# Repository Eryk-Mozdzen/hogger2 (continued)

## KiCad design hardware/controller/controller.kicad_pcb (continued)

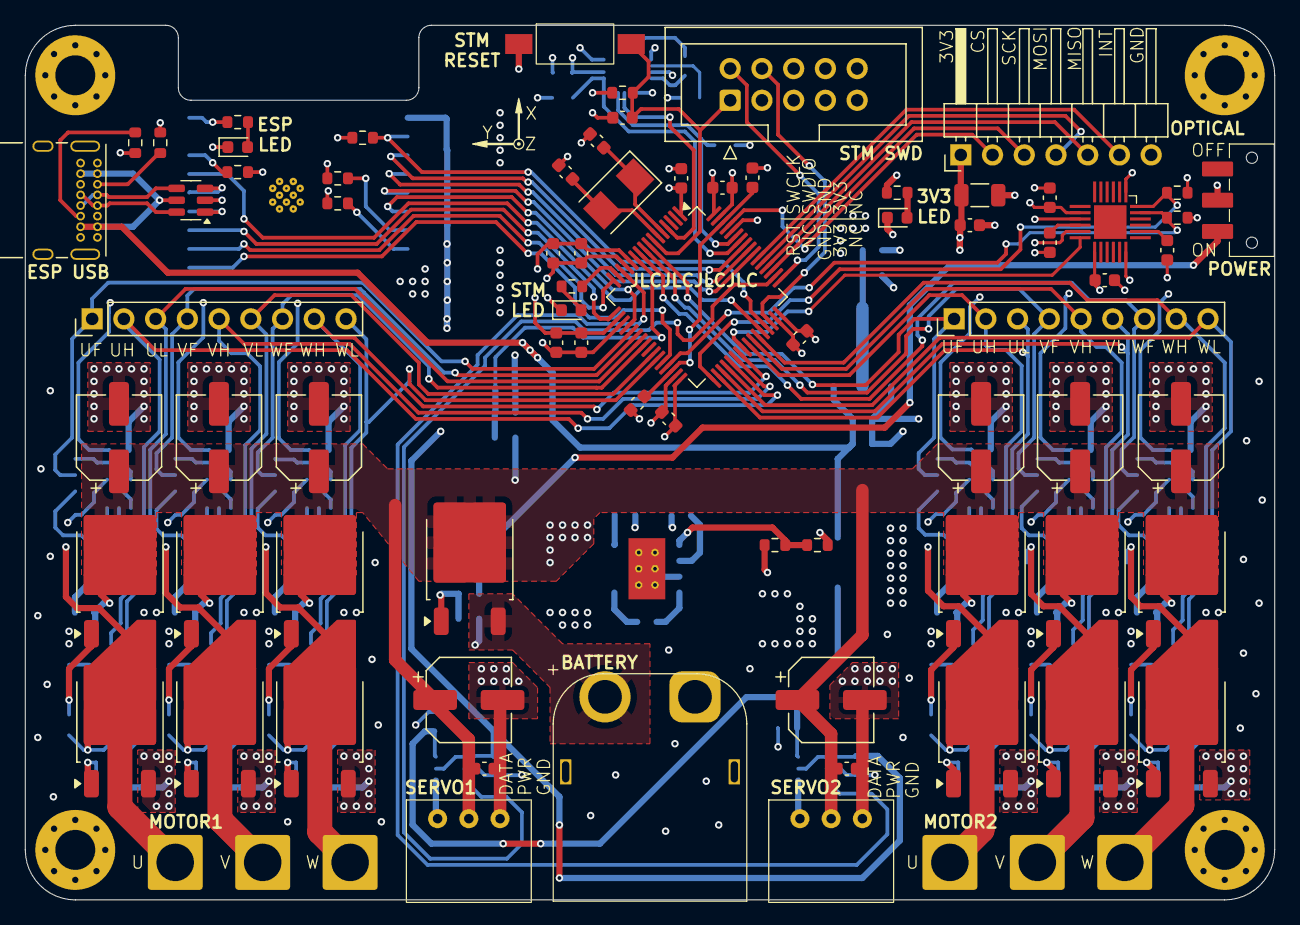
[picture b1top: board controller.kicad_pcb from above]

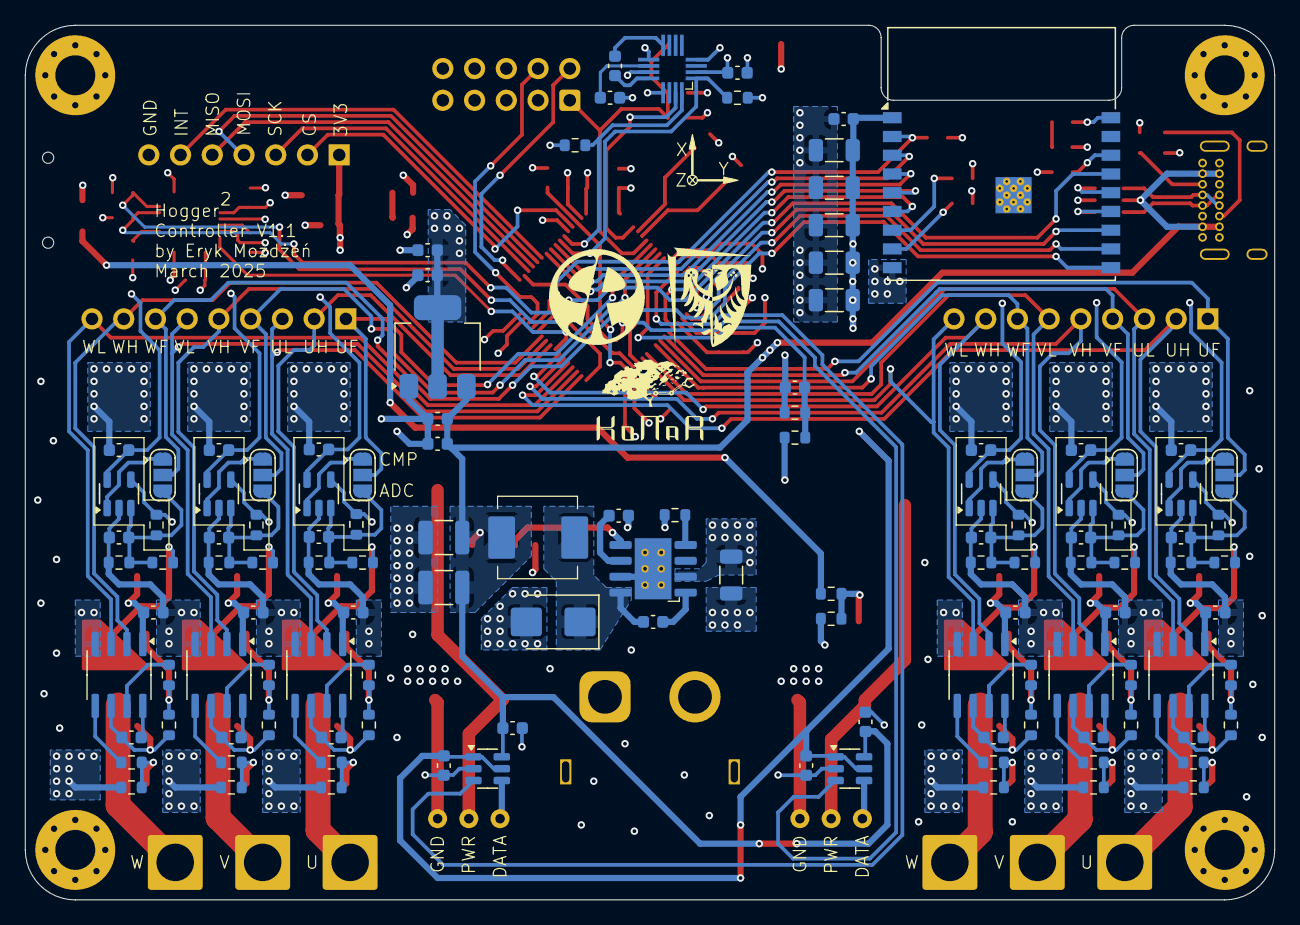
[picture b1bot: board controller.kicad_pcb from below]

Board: 4 copper layers, 100.0 x 70.0 mm, 205 parts (122 on the bottom side), 130 nets.

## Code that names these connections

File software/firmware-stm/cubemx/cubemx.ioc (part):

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Mcu.Name=STM32H523RETx
Mcu.Package=LQFP64
Mcu.UserName=STM32H523RETx
PA0.GPIOParameters=GPIO_Label
PA0.GPIO_Label=SERVO2_DATA
PA0.Mode=Half_duplex(single_wire_mode)
PA0.Signal=UART4_TX
PA1.GPIOParameters=GPIO_Label
PA1.GPIO_Label=LED
PA1.Signal=GPIO_Output
PA10.GPIOParameters=GPIO_Speed,GPIO_Label
PA10.GPIO_Label=MOTOR2_PWM_WH
PA10.GPIO_Speed=GPIO_SPEED_FREQ_LOW
PA10.Signal=S_TIM1_CH3
PA12.GPIOParameters=GPIO_PuPd,GPIO_Label,GPIO_ModeDefaultOutputPP
PA12.GPIO_Label=ESP_EN
PA12.GPIO_ModeDefaultOutputPP=GPIO_MODE_OUTPUT_OD
PA12.GPIO_PuPd=GPIO_NOPULL
PA12.Signal=GPIO_Output
PA15(JTDI).GPIOParameters=GPIO_Label
PA15(JTDI).GPIO_Label=SERVO1_DATA
PA15(JTDI).Mode=Half_duplex(single_wire_mode)
PA15(JTDI).Signal=USART1_TX
PA4.GPIOParameters=GPIO_Label
PA4.GPIO_Label=ESP_CS
PA4.Signal=GPIO_Output
PA5.GPIOParameters=GPIO_Label
PA5.GPIO_Label=MOTOR1_BEMF_U
PA5.Signal=ADCx_INP19
PA6.GPIOParameters=GPIO_Label
PA6.GPIO_Label=MOTOR1_BEMF_V
PA6.Signal=ADCx_INP3
PA7.GPIOParameters=GPIO_Speed,GPIO_Label
PA7.GPIO_Label=MOTOR1_PWM_UL
PA7.GPIO_Speed=GPIO_SPEED_FREQ_LOW
PA7.Mode=PWM Generation1 CH1 CH1N
PA7.Signal=TIM8_CH1N
PA8.GPIOParameters=GPIO_Speed,GPIO_Label
PA8.GPIO_Label=MOTOR2_PWM_UH
PA8.GPIO_Speed=GPIO_SPEED_FREQ_LOW
PA8.Signal=S_TIM1_CH1
PA9.GPIOParameters=GPIO_Speed,GPIO_Label
PA9.GPIO_Label=MOTOR2_PWM_VH
PA9.GPIO_Speed=GPIO_SPEED_FREQ_LOW
PA9.Signal=S_TIM1_CH2
PB0.GPIOParameters=GPIO_Speed,GPIO_Label
PB0.GPIO_Label=MOTOR1_PWM_VL
PB0.GPIO_Speed=GPIO_SPEED_FREQ_LOW
PB0.Mode=PWM Generation2 CH2 CH2N
PB0.Signal=TIM8_CH2N
PB1.GPIOParameters=GPIO_Speed,GPIO_Label
PB1.GPIO_Label=MOTOR1_PWM_WL
PB1.GPIO_Speed=GPIO_SPEED_FREQ_LOW
PB1.Mode=PWM Generation3 CH3 CH3N
PB1.Signal=TIM8_CH3N
PB10.GPIOParameters=GPIO_Label
PB10.GPIO_Label=IMU_SCL
PB10.Mode=I2C
PB10.Signal=I2C2_SCL
PB12.GPIOParameters=GPIO_Label
PB12.GPIO_Label=IMU_SDA
PB12.Mode=I2C
PB12.Signal=I2C2_SDA
PB13.GPIOParameters=GPIO_Speed,GPIO_Label
PB13.GPIO_Label=MOTOR2_PWM_UL
PB13.GPIO_Speed=GPIO_SPEED_FREQ_LOW
PB13.Mode=PWM Generation1 CH1 CH1N
PB13.Signal=TIM1_CH1N
PB14.GPIOParameters=GPIO_Speed,GPIO_Label
PB14.GPIO_Label=MOTOR2_PWM_VL
PB14.GPIO_Speed=GPIO_SPEED_FREQ_LOW
PB14.Mode=PWM Generation2 CH2 CH2N
PB14.Signal=TIM1_CH2N
PB15.GPIOParameters=GPIO_Speed,GPIO_Label
PB15.GPIO_Label=MOTOR2_PWM_WL
PB15.GPIO_Speed=GPIO_SPEED_FREQ_LOW
PB15.Mode=PWM Generation3 CH3 CH3N
PB15.Signal=TIM1_CH3N
PB2.GPIOParameters=GPIO_Label
PB2.GPIO_Label=ESP_HANDSHAKE
PB2.Signal=GPXTI2
PB3(JTDO/TRACESWO).GPIOParameters=GPIO_Label
PB3(JTDO/TRACESWO).GPIO_Label=ESP_SCK
PB3(JTDO/TRACESWO).Mode=Full_Duplex_Master
PB3(JTDO/TRACESWO).Signal=SPI1_SCK
PB4(NJTRST).GPIOParameters=GPIO_Label
PB4(NJTRST).GPIO_Label=ESP_MISO
PB4(NJTRST).Mode=Full_Duplex_Master
PB4(NJTRST).Signal=SPI1_MISO
PB5.GPIOParameters=GPIO_Label
PB5.GPIO_Label=ESP_MOSI
PB5.Mode=Full_Duplex_Master
PB5.Signal=SPI1_MOSI
PB6.GPIOParameters=GPIO_Label
PB6.GPIO_Label=MAG_SCL
PB6.Mode=I2C
PB6.Signal=I2C1_SCL
PB7.GPIOParameters=GPIO_Label
PB7.GPIO_Label=MAG_SDA
PB7.Mode=I2C
PB7.Signal=I2C1_SDA
PB8.GPIOParameters=GPIO_Label
PB8.GPIO_Label=FLOW_CS
PB8.Signal=GPIO_Output
PC0.GPIOParameters=GPIO_Label
PC0.GPIO_Label=MOTOR2_BEMF_U
PC0.Signal=ADCx_INP10
PC1.GPIOParameters=GPIO_Label
PC1.GPIO_Label=MOTOR2_BEMF_V
PC1.Signal=ADCx_INP11
PC10.GPIOParameters=GPIO_Label
PC10.GPIO_Label=FLOW_SCK
PC10.Mode=Full_Duplex_Master
PC10.Signal=SPI3_SCK
PC11.GPIOParameters=GPIO_Label
PC11.GPIO_Label=FLOW_MISO
PC11.Mode=Full_Duplex_Master
PC11.Signal=SPI3_MISO
PC12.GPIOParameters=GPIO_Label
PC12.GPIO_Label=FLOW_MOSI
PC12.Mode=Full_Duplex_Master
PC12.Signal=SPI3_MOSI
PC15-OSC32_OUT(OSC32_OUT).GPIOParameters=GPIO_Label,GPIO_ModeDefaultEXTI
PC15-OSC32_OUT(OSC32_OUT).GPIO_Label=MAG_INT
PC15-OSC32_OUT(OSC32_OUT).GPIO_ModeDefaultEXTI=GPIO_MODE_IT_RISING
PC15-OSC32_OUT(OSC32_OUT).Signal=GPXTI15
PC2.GPIOParameters=GPIO_Label
PC2.GPIO_Label=MOTOR2_BEMF_W
PC2.Signal=ADCx_INP12
PC3.GPIOParameters=GPIO_Label
PC3.GPIO_Label=VBUS_SENSE
PC3.Signal=ADCx_INP13
PC4.GPIOParameters=GPIO_Label
PC4.GPIO_Label=MOTOR1_BEMF_W
PC4.Signal=ADCx_INP4
PC6.GPIOParameters=GPIO_Speed,GPIO_Label
PC6.GPIO_Label=MOTOR1_PWM_UH
PC6.GPIO_Speed=GPIO_SPEED_FREQ_LOW
PC6.Signal=S_TIM8_CH1
PC7.GPIOParameters=GPIO_Speed,GPIO_Label
PC7.GPIO_Label=MOTOR1_PWM_VH
PC7.GPIO_Speed=GPIO_SPEED_FREQ_LOW
PC7.Signal=S_TIM8_CH2
PC8.GPIOParameters=GPIO_Speed,GPIO_Label
PC8.GPIO_Label=MOTOR1_PWM_WH
PC8.GPIO_Speed=GPIO_SPEED_FREQ_LOW
PC8.Signal=S_TIM8_CH3
PC9.GPIOParameters=GPIO_Label,GPIO_ModeDefaultEXTI
PC9.GPIO_Label=IMU_INT
PC9.GPIO_ModeDefaultEXTI=GPIO_MODE_IT_RISING
PC9.Signal=GPXTI9
PH0-OSC_IN(PH0).Mode=HSE-External-Oscillator
PH0-OSC_IN(PH0).Signal=RCC_OSC_IN
PH1-OSC_OUT(PH1).Mode=HSE-External-Oscillator
PH1-OSC_OUT(PH1).Signal=RCC_OSC_OUT
RCC.HSE_VALUE=8000000
RCC.SYSCLKFreq_VALUE=250000000
RCC.SYSCLKSource=RCC_SYSCLKSOURCE_PLLCLK
board=custom

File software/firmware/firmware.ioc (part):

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Mcu.Name=STM32U535RETx
Mcu.Package=LQFP64
Mcu.UserName=STM32U535RETx
PA10.GPIOParameters=GPIO_Label
PA10.GPIO_Label=MOTOR1_PWM_WH
PA10.Signal=S_TIM1_CH3
PA8.GPIOParameters=GPIO_Label
PA8.GPIO_Label=MOTOR1_PWM_UH
PA8.Signal=S_TIM1_CH1
PA9.GPIOParameters=GPIO_Label
PA9.GPIO_Label=MOTOR1_PWM_VH
PA9.Signal=S_TIM1_CH2
PB13.GPIOParameters=GPIO_Label
PB13.GPIO_Label=MOTOR1_PWM_UL
PB13.Mode=PWM Generation1 CH1 CH1N
PB13.Signal=TIM1_CH1N
PB14.GPIOParameters=GPIO_Label
PB14.GPIO_Label=MOTOR1_PWM_VL
PB14.Mode=PWM Generation2 CH2 CH2N
PB14.Signal=TIM1_CH2N
PB15.GPIOParameters=GPIO_Label
PB15.GPIO_Label=MOTOR1_PWM_WL
PB15.Mode=PWM Generation3 CH3 CH3N
PB15.Signal=TIM1_CH3N
PB2.GPIOParameters=GPIO_Label,GPIO_ModeDefaultEXTI
PB2.GPIO_Label=MOTOR1_BEMF_W
PB2.GPIO_ModeDefaultEXTI=GPIO_MODE_IT_RISING_FALLING
PB2.Signal=GPXTI2
PB5.GPIOParameters=GPIO_Label
PB5.GPIO_Label=LED
PB5.Signal=GPIO_Output
PB6.GPIOParameters=GPIO_Label
PB6.GPIO_Label=ESP_RXD
PB6.Mode=Asynchronous
PB6.Signal=USART1_TX
PB7.GPIOParameters=GPIO_Label
PB7.GPIO_Label=ESP_TXD
PB7.Mode=Asynchronous
PB7.Signal=USART1_RX
PC0.GPIOParameters=GPIO_Label,GPIO_ModeDefaultEXTI
PC0.GPIO_Label=MOTOR1_BEMF_U
PC0.GPIO_ModeDefaultEXTI=GPIO_MODE_IT_RISING_FALLING
PC0.Signal=GPXTI0
PC1.GPIOParameters=GPIO_Label,GPIO_ModeDefaultEXTI
PC1.GPIO_Label=MOTOR1_BEMF_V
PC1.GPIO_ModeDefaultEXTI=GPIO_MODE_IT_RISING_FALLING
PC1.Signal=GPXTI1
PC2.GPIOParameters=GPIO_PuPd
PC2.GPIO_PuPd=GPIO_PULLUP
PC2.Signal=GPIO_Input
PH0-OSC_IN\ (PH0).Mode=HSE-External-Oscillator
PH0-OSC_IN\ (PH0).Signal=RCC_OSC_IN
PH1-OSC_OUT\ (PH1).Mode=HSE-External-Oscillator
PH1-OSC_OUT\ (PH1).Signal=RCC_OSC_OUT
RCC.HSE_VALUE=8000000
RCC.SYSCLKFreq_VALUE=160000000
RCC.SYSCLKSource=RCC_SYSCLKSOURCE_PLLCLK
board=custom

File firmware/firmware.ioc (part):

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Mcu.Name=STM32U535RETx
Mcu.Package=LQFP64
Mcu.UserName=STM32U535RETx
PA1.GPIOParameters=GPIO_Label
PA1.GPIO_Label=R_SERVO_Y
PA1.Signal=S_TIM5_CH2
PA10.GPIOParameters=GPIO_Label
PA10.GPIO_Label=R_SERVO_X
PA10.Signal=S_TIM1_CH3
PA11.GPIOParameters=GPIO_Label
PA11.GPIO_Label=L_MOTOR
PA11.Signal=S_TIM1_CH4
PA2.GPIOParameters=GPIO_Label
PA2.GPIO_Label=R_MOTOR
PA2.Signal=S_TIM5_CH3
PA8.GPIOParameters=GPIO_Label
PA8.GPIO_Label=L_SERVO_X
PA8.Signal=S_TIM1_CH1
PA9.GPIOParameters=GPIO_Label
PA9.GPIO_Label=L_SERVO_Y
PA9.Signal=S_TIM1_CH2
PB2.GPIOParameters=GPIO_Label
PB2.GPIO_Label=LED
PB2.Signal=GPIO_Output
PC10.Mode=Asynchronous
PC10.Signal=UART4_TX
PC11.Mode=Asynchronous
PC11.Signal=UART4_RX
PH0-OSC_IN\ (PH0).Mode=HSE-External-Oscillator
PH0-OSC_IN\ (PH0).Signal=RCC_OSC_IN
PH1-OSC_OUT\ (PH1).Mode=HSE-External-Oscillator
PH1-OSC_OUT\ (PH1).Signal=RCC_OSC_OUT
RCC.HSE_VALUE=8000000
RCC.SYSCLKFreq_VALUE=160000000
RCC.SYSCLKSource=RCC_SYSCLKSOURCE_PLLCLK
board=custom

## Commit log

2024-10-15 sine control PWM
2024-10-16 simple PC app for control and offset
2024-10-17 work
2024-10-23 side to side motion
2024-10-23 Full Model (2) IO-decoupling with static linearization
2024-10-23 add arrows
2024-10-28 start of hardware design
2024-10-28 add IMU, FLOW, 5V, 3.3V, MOSFET SW
2024-10-28 move code to software folder
2024-10-29 add architecture
2024-10-30 power stage development #1
2024-10-31 remove current sensing, external MOSFET diodes, BEMF filteringadd MOSFETs
2024-11-01 uC pinout and second power stage
2024-11-01 remove current from architecture
2024-11-01 change P-MOSFET on the battery enter
2024-11-03 footprints, layout
2024-11-05 add VBUS sense to STM and ESP, change buttons and sw to vertical, add USB-C to SEM
2024-11-05 fix voltage divider
2024-11-06 USBLC6, IR2101
2024-11-06 custom footprints with all 3D models
2024-11-09 back to LM2105, remove USB-C from STM
2024-11-09 update date
2024-11-09 first real layout, change comps to MCP6541
2024-11-10 full layout, edge power switch
2024-11-11 routing
2024-11-11 add silkscreen layer
2024-11-19 gitignore gerbers and BOM
2024-11-27 use diffrent P-MOSFET
2024-11-27 bigger capacitors on step down
2024-12-08 add uc docs
2024-12-08 6 step 100Hz
2024-12-16 add button, G resistors 68ohm, additional 47kohm between G and S
2024-12-23 motor development
2024-12-25 working open-loop
2024-12-26 magic smoke again
2024-12-26 100nF as BEMF filter
2024-12-28 forst CLOSED LOOP work!
2024-12-29 working velocity control
2024-12-30 working open loop ramp
2024-12-31 commut timer with hardware TRGO, single PID
2025-01-02 simpler ramp calculations (us)
2025-01-02 start ESP firmware development
2025-01-04 ESP32C3 UART-HTTP bridge using custom Goose-II protocol
2025-01-04 sync blink
2025-01-04 CMake based project + just STM32CubeMX, fix protocol/DMA modulo BUG
2025-01-04 input/output JSON
2025-01-05 read battery voltage
2025-01-05 new station app
2025-01-06 remove unused fragments of protocol, faster ESP communication, fix station UI
2025-01-06 MessagePack on UART, JSON on network
2025-01-06 fix station json
2025-01-06 UART on 230400, shorter names in JSON
2025-01-07 firmware work for both motors
2025-01-07 read IMU
2025-01-08 add FLOW sensor
2025-01-11 introduction of Lightweight Robust Communication Protocol (LRCP)
2025-01-11 better serial transmit
2025-01-11 split serialization and sensors to separate files
2025-01-11 add servos
2025-01-11 open-loop RC control
2025-01-12 update docs
2025-01-13 fir control
2025-01-19 imporve station app HTTP latency
2025-01-19 better image
2025-01-22 fix wheel direction and controls
2025-01-24 UDP+TCP sockets
2025-01-24 UDP in both ways
2025-01-25 faster motors
2025-01-26 very simple close-loop control
2025-01-26 station watchdog
2025-01-26 improve motor control again
2025-02-02 add final report for Intermediate Project
2025-02-22 wip - placement
2025-03-02 FreeRTOS with C++
2025-03-02 mailbox
2025-03-04 drive like a dream
2025-03-05 C style architecture (need test)
2025-03-07 mpack dev
2025-03-08 config and NVM
2025-03-08 wip elements
2025-03-08 wip routing power stages
2025-03-08 wip - motor and ESP signals
2025-03-09 new GCC C23
2025-03-09 task triggers
2025-03-09 wip better pinout
2025-03-09 wip - ready, but need double check
2025-03-09 more stuff without tests
2025-03-10 remove segfaults
2025-03-10 auto config works?
2025-03-11 working servos
2025-03-11 flow works
2025-03-11 migrate to new cubemx
2025-03-12 migrate to kicad 9
2025-03-12 check and fix DRC errors
2025-03-12 generate schematic in PDF
2025-03-13 microsecond periodic task timebase, core load measurement, ICACHE
2025-03-13 newer ESP IDF
2025-03-13 move scripts out
2025-03-14 add estimator submodule
2025-03-14 state estimation using imu and flow
2025-03-16 zeromq bridge, live-plots from Goose-II, python script for manual control
2025-03-16 python script for visualizer, correct optical flow plot, optical flow gyro-compensation
2025-03-16 python app for trajectory generation
2025-03-16 reset ekf, capacitor on PMW3901
2025-03-21 add led datasheet
2025-03-22 ported motors and dead time calculator
2025-03-23 timebase work
2025-03-23 motor 1 work
2025-03-24 switch and ESP work
2025-03-24 port calibration app from Goose-II
2025-03-24 calib fix JSON update
2025-03-24 fix segfault on QThreads
2025-03-24 add back rest of the code (need check)
2025-03-24 add back control
2025-03-24 timer timebase
2025-03-24 fix mag correction
2025-03-26 IMU use calibration values, sending raw and out
2025-03-26 reading raw and out, separate scale and offset
2025-03-26 IMU, MAG, FLOW, battery, servos work
2025-03-26 config WIP, robot work as before
2025-03-27 calibration work?
2025-03-27 lemniscate trajectory generator
2025-03-28 working FLASH read/write, better ACC calibration sampling
2025-03-28 fix MAG calibration sampling, fix EKF reset yaw
2025-03-29 better MAG ellipsoid fitting
2025-03-29 more intuitive MAG least squares
2025-03-30 bidirectional BLDC, actuator setpoint validation, correct actuator directions like in mathematical model
2025-03-30 fix motor dir in trajectory
2025-04-01 update architecture
2025-04-02 fix arch
2025-04-03 Drake simulation
2025-04-04 dynamic feedback linearization for poor full model
2025-04-05 Joniak's scripts
2025-04-05 work driftless q=Gn full model
2025-04-05 JPTD for FULL not work, JPTD for JPTD work little bit
2025-04-06 add Boczar's scripts
2025-04-06 better code generation, Kdd obtained just from h2.jacobion(u)
2025-04-07 JPTD work on FULL model!
2025-04-08 trajectory write/read/interpolation
2025-04-09 nicer controller code, plots for interpolation
2025-04-10 almost work?
2025-04-11 esp -O2 + handshake
2025-04-11 cleaning
2025-04-12 rename signals to correct
2025-04-12 predefined set of trajetories
2025-04-13 controller is not blowing up
2025-04-13 first tests of trajectory tracking
2025-04-18 trajectory smoother
2025-04-19 7-degree poly as smooth function
2025-04-20 trajectory smoothing
2025-04-20 check DATA READY flag when reading OPTICAL FLOW
2025-04-21 add servo offsets in CONFIG
2025-04-21 NDJSON database recorder
2025-04-23 second tests
2025-04-23 plotter for saved NDJSON databases
2025-04-23 better plots
2025-04-24 new servo calibration method? NEED test with JPTD
2025-04-29 controller JPTD 1D and naive, FIX INTEGRATION DT, separate trajectory, separate integrator
2025-04-30 first correct circle
2025-04-30 generators generated by sympy
2025-05-01 JPTD dynamic dev
2025-05-02 partial calibration read/write
2025-05-03 simplified static online dev
2025-05-10 nie wiem czemu to dziadostwo nie działa
2025-05-11 state vector estiamtion from HOG1
2025-05-11 dodałem simplified static online ale w symulacji nie działa i tak...
2025-05-12 PID controller just works
2025-05-14 clear PID cascade implementation, filter, step experiments, ready for tests
2025-05-14 add PID autotune script
2025-05-15 tune all PIDs from step responses
2025-05-16 PID autotuner script
2025-05-17 autotunning PIDs for motors
2025-05-17 smooth lemistate inner PI outer PI no filter
2025-05-17 better PID lambda method for integrating plant
2025-05-21 improved EKF
2025-05-21 fix motor vel number of pole pairs
2025-05-21 add best records
2025-05-23 higher optical flow, new KAVAN motors, maybe EKF will work
2025-05-23 add motors step record
2025-05-25 add const
2025-05-26 plastic wheels
2025-05-26 plastic wheels steps
2025-05-26 EKF fixed? IMU and MAG fixed 400kHz I2C
2025-05-27 PID cascade works PERFECTLY
2025-05-27 JPTD WORKS XD
2025-05-27 turn off brown-out detection in ESP32C3
2025-05-30 CSV generation for master thesis
2025-06-04 align J8 and J12 on schematic
2025-06-07 print also inertial end
2025-06-09 print matrices for dynamic linearization
2025-06-13 renaming to amtch thesis, PID with Tu transform, LISSAJOUS trajectory from Joniak
2025-06-13 better outer Y tunning, fix lissajous
2025-06-13 fix motors velocity plotting
2025-06-13 SIMULTANOUS NAIVE work for identical and mirrored controls
2025-06-14 matplotlib for thesis
2025-06-14 jeszcze
2025-06-14 add servo offset to telemetry
2025-06-14 add plot generation for thesis
2025-06-16 experiments to the thesis
2025-06-16 plots
2025-06-16 first thesis plots
2025-06-19 plots match thesis font size
2025-06-19 remove motion capture from schematic
2025-06-24 add master thesis
